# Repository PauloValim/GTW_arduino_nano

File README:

Placa compatacta do gateway USB serial (MySensors) usando um arduino nano

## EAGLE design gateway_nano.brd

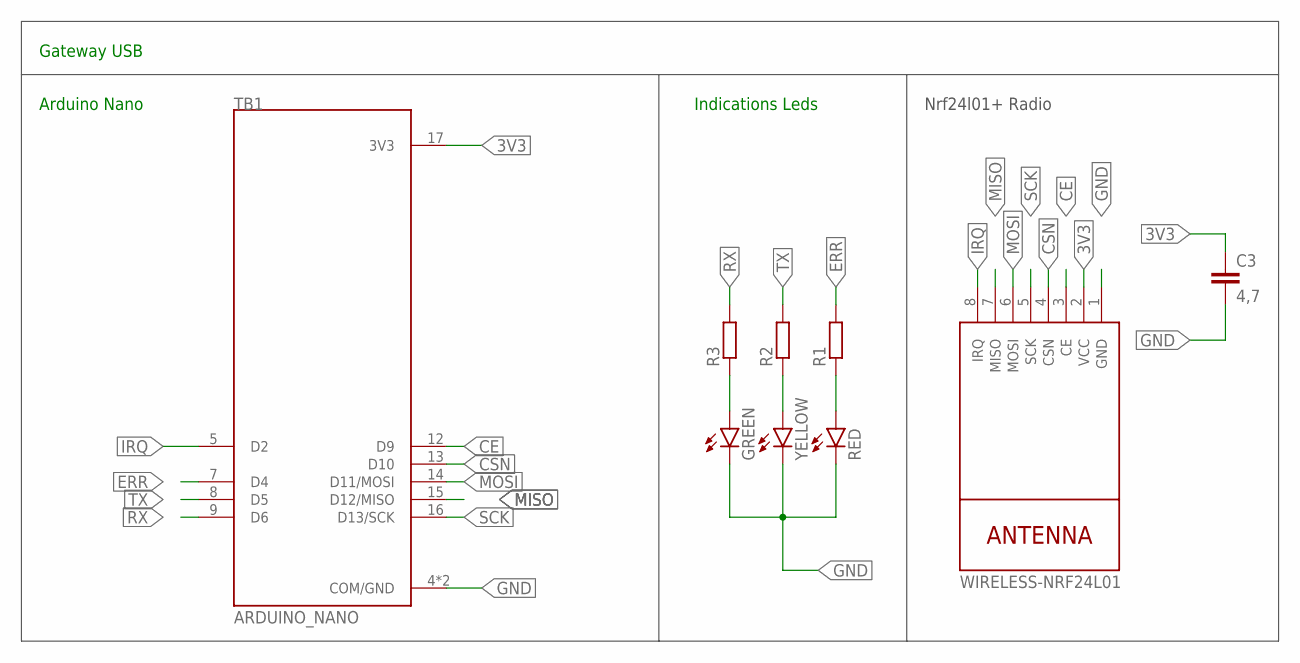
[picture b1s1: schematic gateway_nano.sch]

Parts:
C3: 4,7; C2.5-2
GREEN: LED5MM
NRF24L01+: WIRELESS-NRF24L01
R1, R2, R3: R-EU_R0805; R0805
RED: LED5MM
TB1: ARDUINO_NANO; SHIELD_ARDUINO_NANO
YELLOW: LED5MM

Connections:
3V3: C3.1, NRF24L01+.2 (VCC), TB1.17 (3V3)
CE: NRF24L01+.3 (CE), TB1.12 (D9)
CSN: NRF24L01+.4 (CSN), TB1.13 (D10)
ERR: R1.2, TB1.7 (D4)
GND: C3.2, GREEN.K (C), NRF24L01+.1 (GND), RED.K (C), TB1.4 (COM/GND), TB1.29 (COM/GND), YELLOW.K (C)
IRQ: NRF24L01+.8 (IRQ), TB1.5 (D2)
MISO: NRF24L01+.7 (MISO), TB1.15 (D12/MISO)
MOSI: NRF24L01+.6 (MOSI), TB1.14 (D11/MOSI)
unnamed: R1.1, RED.A
unnamed: R2.1, YELLOW.A
unnamed: GREEN.A, R3.1
RX: R3.2, TB1.9 (D6)
SCK: NRF24L01+.5 (SCK), TB1.16 (D13/SCK)
TX: R2.2, TB1.8 (D5)

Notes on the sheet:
Nrf24l01+ Radio
Gateway USB
Arduino Nano
Indications Leds

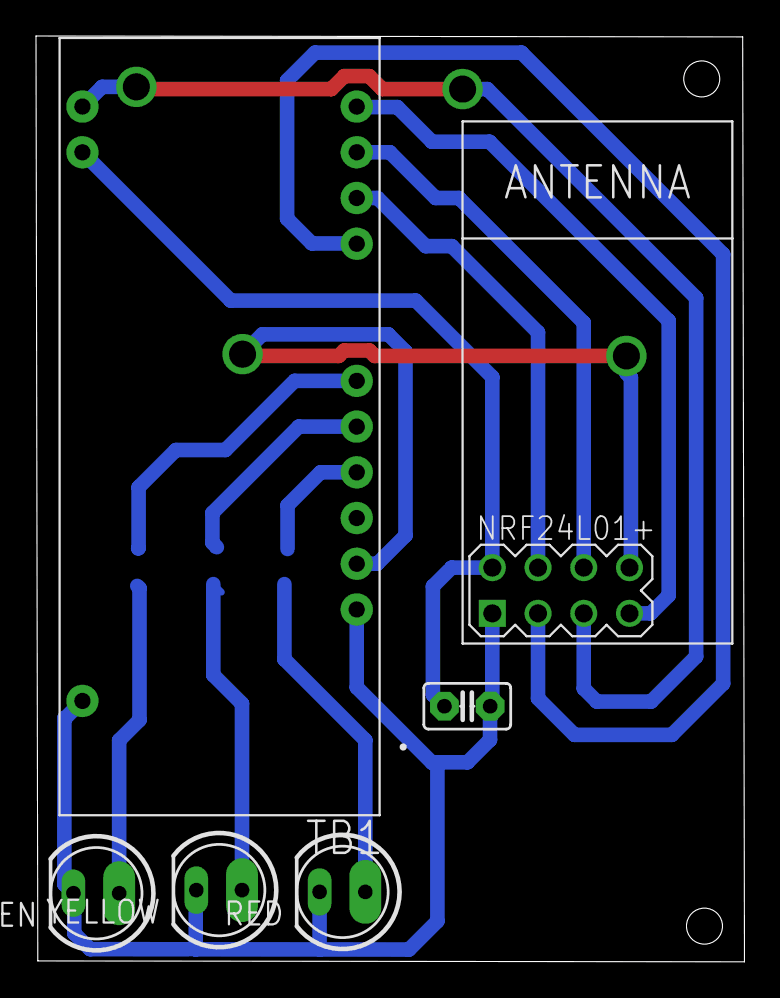
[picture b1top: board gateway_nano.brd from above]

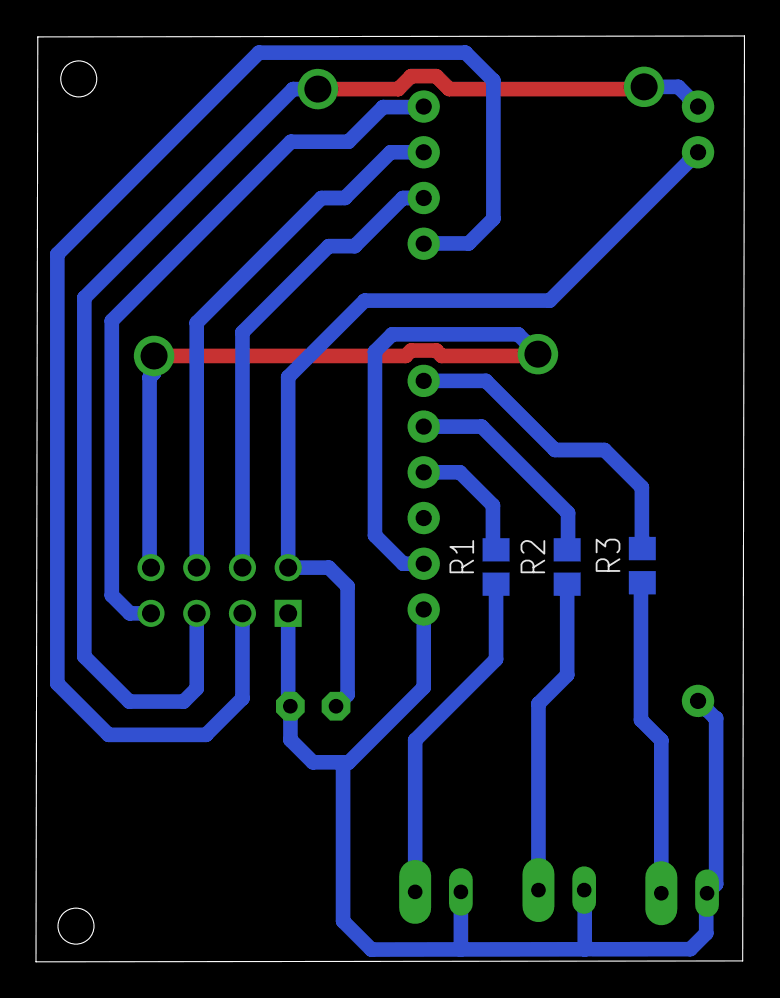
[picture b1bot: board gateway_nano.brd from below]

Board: 2 copper layers, 39.4 x 51.4 mm, 9 parts (3 on the bottom side), 14 nets.

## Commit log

2020-02-08 primeira versao

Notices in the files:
parts and their libraries:
diy-modules: Released under the Creative Commons Attribution 4.0 International License: http://creativecommons.org/licenses/by/4.0
